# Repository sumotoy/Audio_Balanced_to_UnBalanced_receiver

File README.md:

# Audio_Balanced_to_UnBalanced_receiver
A simple monochannel Audio Balanced to UnBalanced receiver based on rocksolid NE5532 and NE5534 but other ic's are possible, it's a simple board, designed to be easily assembled because no SMD and cheap components, the connector on the bottom can be used for wires or (as it was intended) an angled connector for mount board vertically.
There's a trim for change input gain.
This is the first commit and never tested (only on simulator), actually inputs are exposed to overvoltage or DC so if you plan to use in real appliances you need to add input capacitors and/or overvoltage protection extra components.
I plan to use this board for my upcoming studio master controller (this board it's for multichannel musician headphones)
There's an OSH Park PCB you can order.<br>

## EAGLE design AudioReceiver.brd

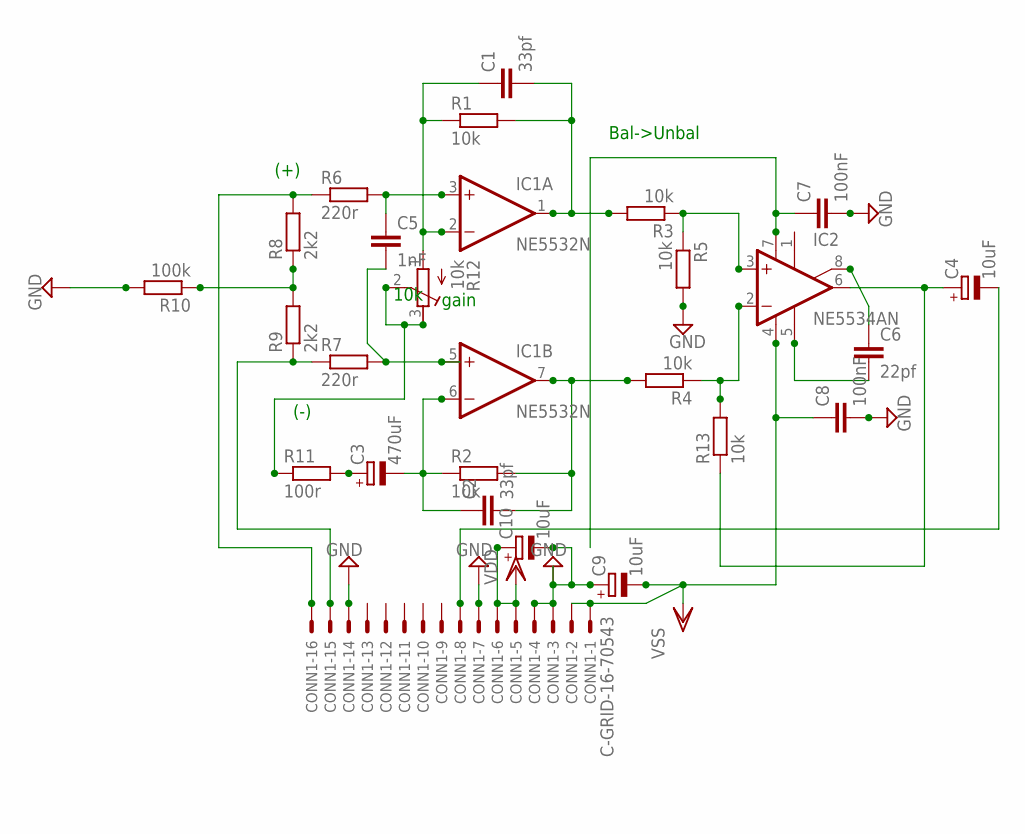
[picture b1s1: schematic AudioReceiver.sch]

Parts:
C1, C2: 33pf; C2.5-2
C3: 470uF; E5-10,5
C4, C9, C10: 10uF; E2,5-5
C5: 1nF; C5B2.5
C6: 22pf; C2.5-2
C7, C8: 100nF; C5B2.5
CONN1: C-GRID-16-70543; 70543-16
IC1: NE5532N; DIL08
IC2: NE5534AN; DIL08
R1, R2, R3, R4, R5, R13: 10k; 0204/7
R6, R7: 220r; 0204/7
R8, R9: 2k2; 0204/7
R10: 100k; 0204/7
R11: 100r; 0204/7
R12: 10k; RTRIM64P

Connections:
GND: C7.2, C8.2, C9.+, C10.-, CONN1.3, CONN1.4, CONN1.7, CONN1.14, R5.2, R10.2
unnamed: C5.1, IC1.3 (+IN), R6.2
unnamed: C6.1, IC2.8 (ON/CMP)
unnamed: C1.2, IC1.1 (OUT), R1.2, R3.2
unnamed: C2.2, IC1.7 (OUT), R2.2, R4.2
unnamed: C1.1, IC1.2 (-IN), R1.1, R12.1 (A)
unnamed: C2.1, C3.-, IC1.6 (-IN), R2.1
unnamed: C3.+, R11.2
unnamed: IC2.3 (+IN), R3.1, R5.1
unnamed: R11.1, R12.2 (S), R12.3 (E)
unnamed: CONN1.15, R7.1, R9.1
unnamed: CONN1.16, R6.1, R8.2
unnamed: R8.1, R9.2, R10.1
unnamed: C5.2, IC1.5 (+IN), R7.2
unnamed: IC2.2 (-IN), R4.1, R13.2
unnamed: C4.+, IC2.6 (OUT), R13.1
unnamed: C6.2, IC2.5 (CMP)
OUT: C4.-, CONN1.8
V+: C7.1, C10.+, CONN1.5, CONN1.6, IC1.8 (V+), IC2.7 (V+)
V-: C8.1, C9.-, CONN1.1, CONN1.2, IC1.4 (V-), IC2.4 (V-)

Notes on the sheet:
Bal->Unbal
(+)
(-)
gain

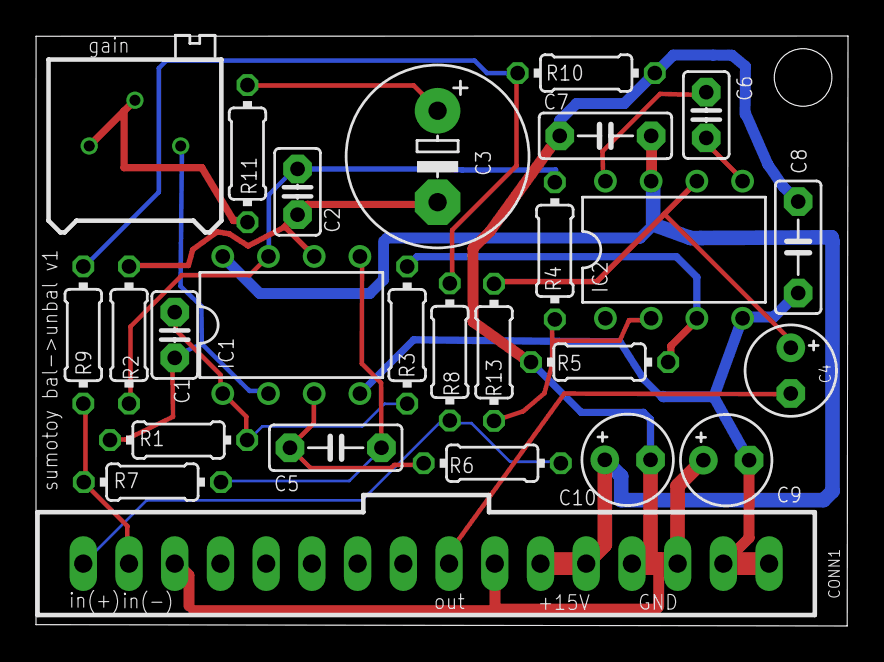
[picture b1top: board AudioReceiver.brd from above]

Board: 2 copper layers, 45.1 x 32.8 mm, 26 parts (0 on the bottom side), 20 nets.

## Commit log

2015-11-24 :circus_tent: Added .gitattributes & .gitignore files
2015-11-24 first commit, uploaded eagle files
2015-11-24 added images
